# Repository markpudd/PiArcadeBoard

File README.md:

PiArcadeBoard
=============

This board provide a SPI based interface for arcade controls to the Raspberry Pi.  

More info on http://makicity.com.

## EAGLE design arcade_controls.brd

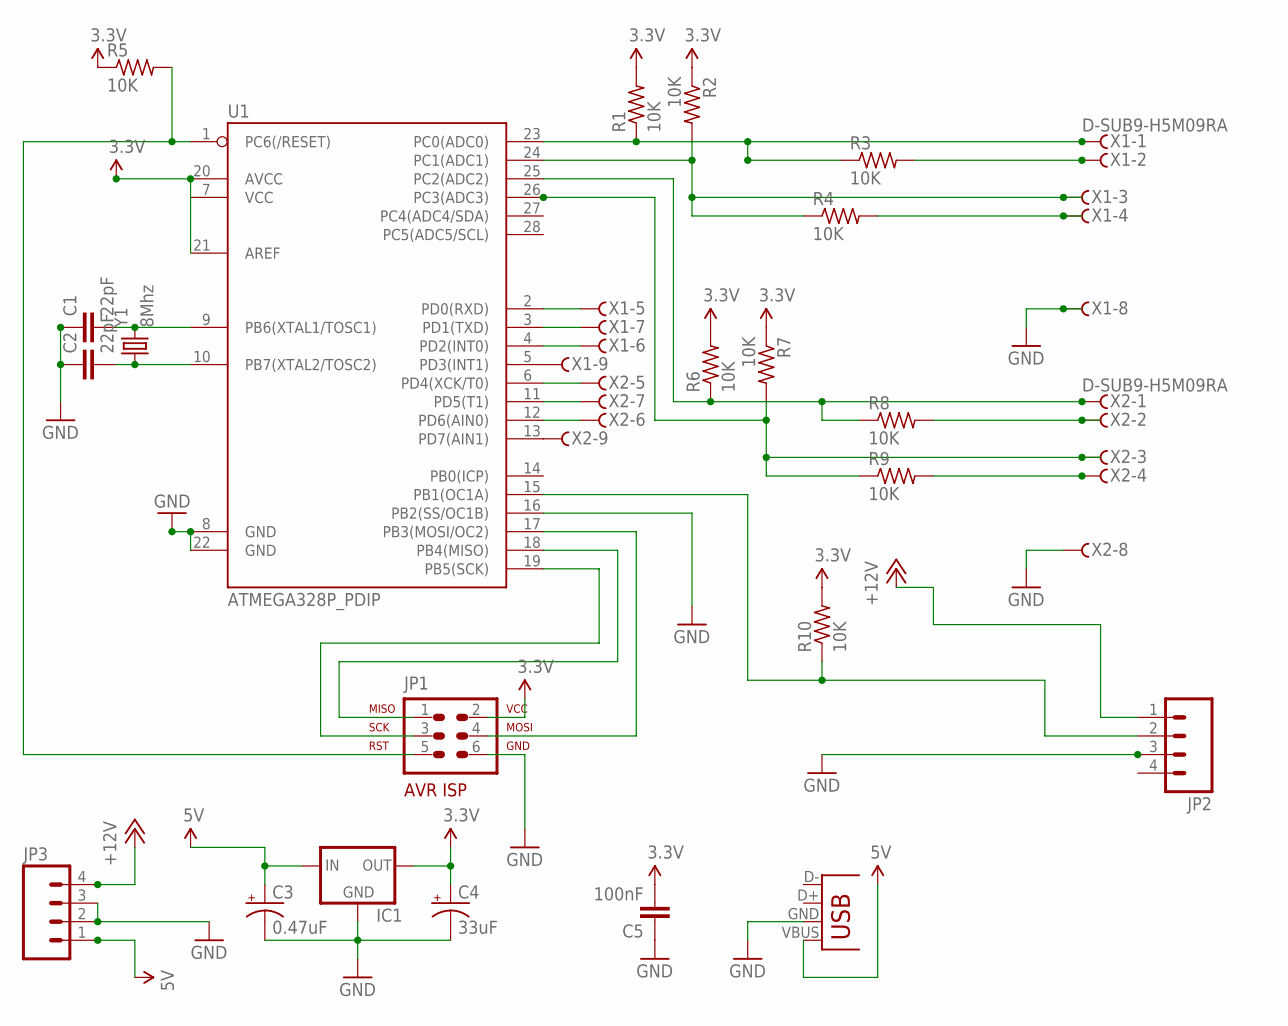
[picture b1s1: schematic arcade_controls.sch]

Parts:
C1, C2: 22pF; CAP-PTH-SMALL
C3: 0.47uF; CPOL-RADIAL-10UF-25V
C4: 33uF; CPOL-RADIAL-10UF-25V
C5: 100nF; CAP-PTH-SMALL
IC1: V_REG_78XXSIDE; 78XXL
JP1: AVR-ISP-6VERT; AVR-ISP-6
JP2, JP3: M04LOCK; 1X04_LOCK
JP4: USB-A-H
R1, R2, R3, R4, R5, R6, R7, R8, R9, R10: 10K; 0309/12
U1: ATMEGA328P_PDIP; DIL28-3
X1, X2: D-SUB9-H5M09RA; H5M09RA
Y1: 8Mhz; HC49U-V

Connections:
3.3V: C4.1 (+), C5.2, IC1.OUT, JP1.2, R1.2, R2.1, R5.1, R6.2, R7.1, R10.2, U1.7 (VCC), U1.20 (AVCC), U1.21 (AREF)
5V: C3.1 (+), IC1.IN, JP3.1, JP4.VBUS (GND)
+12V: JP2.1, JP3.4
GND: C1.1, C2.1, C3.2 (-), C4.2 (-), C5.1, IC1.GND, JP1.6, JP2.3, JP3.2, JP3.3, JP4.GND (VBUS), U1.8 (GND), U1.16 (PB2(SS/OC1B)), U1.22 (GND), X1.8, X2.8
unnamed: R1.1, R3.1, U1.23 (PC0(ADC0)), X1.1
unnamed: U1.12 (PD6(AIN0)), X2.6
unnamed: JP1.5, R5.2, U1.1 (PC6(/RESET))
unnamed: R2.2, R4.1, U1.24 (PC1(ADC1)), X1.3
unnamed: JP1.3, U1.19 (PB5(SCK))
unnamed: JP1.1, U1.18 (PB4(MISO))
unnamed: JP1.4, U1.17 (PB3(MOSI/OC2))
unnamed: U1.13 (PD7(AIN1)), X2.9
unnamed: C2.2, U1.10 (PB7(XTAL2/TOSC2)), Y1.1
unnamed: JP2.2, R10.1, U1.15 (PB1(OC1A))
unnamed: U1.11 (PD5(T1)), X2.7
unnamed: R3.2, X1.2
unnamed: R4.2, X1.4
unnamed: U1.3 (PD1(TXD)), X1.7
unnamed: R7.2, R9.1, U1.26 (PC3(ADC3)), X2.3
unnamed: C1.2, U1.9 (PB6(XTAL1/TOSC1)), Y1.2
unnamed: R6.1, R8.1, U1.25 (PC2(ADC2)), X2.1
unnamed: R8.2, X2.2
unnamed: R9.2, X2.4
unnamed: U1.2 (PD0(RXD)), X1.5
unnamed: U1.4 (PD2(INT0)), X1.6
unnamed: U1.5 (PD3(INT1)), X1.9
unnamed: U1.6 (PD4(XCK/T0)), X2.5

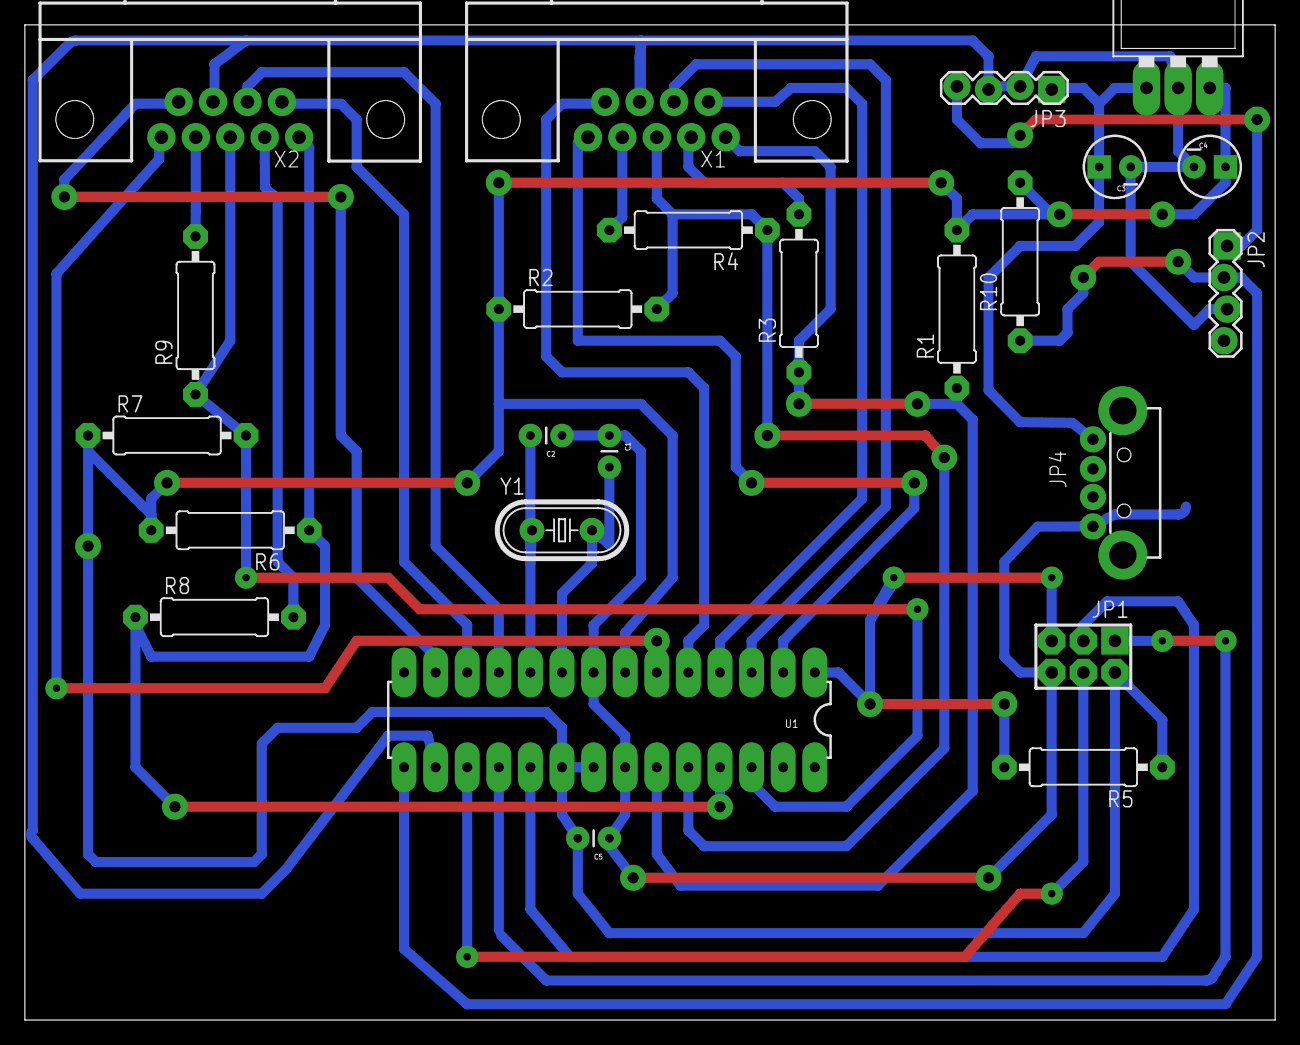
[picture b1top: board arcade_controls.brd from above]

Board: 2 copper layers, 100.5 x 80.0 mm, 24 parts (0 on the bottom side), 27 nets.

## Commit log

2014-06-15 Initial version

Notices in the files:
parts and their libraries:
SparkFun-FreqCtrl: Licensing: CC v3.0 Share-Alike You are welcome to use this library for commercial purposes.
